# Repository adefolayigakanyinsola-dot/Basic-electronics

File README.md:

# Basic-electronics
Projects covering introduction to electronic components and systems
# Touch Enabled Circuit Design
A non microcontroller electronics project that lights up the LED when two insulated wires touch each other at the same time.
# Project Description
It is a simple project built on a breadboard. When two bare wires which serves as connectors are touched at the same time, a small amount of elevtricity passes through the skin due to low conductivity and high resistance. This in turn causes the transisitor to come on. The transistor then produces a large current from the base and battery combined which triggers the flow of current from the collector to the emitter.Then the current is passed into the LED to turn it on.

# INSTALLATION  PROCESS
# Software - KICAD
After creating a new file and nameing the circuit design,draw the schematics.
To do this,click on the component symbol icon on the top right icon bar to the side and select the components.
Use the mouse to drag and connect the wires accordingly.
Assign footprints by using the upper ico to the right on the menu bar or left click the mouse on each component,then navigate to footprints to check for suitable type of footprint component.
# PCB LAYOUT
Open the PCB bar by clicking on the default icon which is top right to the extreme,it takes you to thr layout that has all the components layout in PCB.
Using edge cuts in the apperance icon to the right,draw the small board outline enough to cover the circuit.
Arrange the components and usd the route signals to connect them 
Using the view icon in the top left icon on the menu bar,check the 3D layout.

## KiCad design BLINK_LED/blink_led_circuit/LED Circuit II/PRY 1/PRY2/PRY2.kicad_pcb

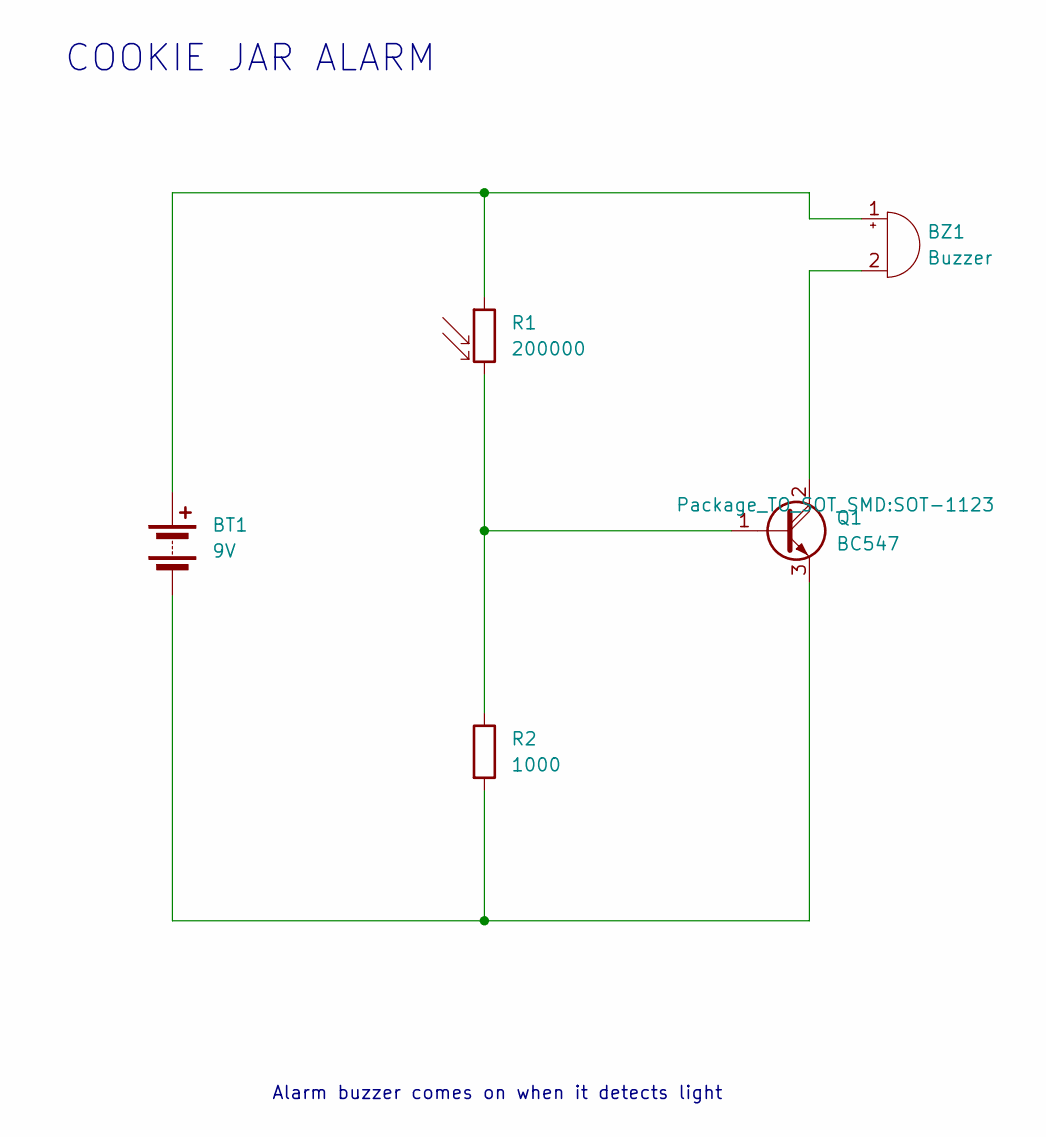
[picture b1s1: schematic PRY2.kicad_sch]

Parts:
BT1: 9V; BatteryHolder_MYOUNG_BS-07-A1BJ001_CR2032
BZ1: Buzzer; Buzzer_15x7.5RM7.6
Q1: BC547; SOT-1123
R1: 200000; R_LDR_10x8.5mm_P7.6mm_Vertical
R2: 1000; R_Axial_DIN0204_L3.6mm_D1.6mm_P5.08mm_Horizontal

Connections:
unnamed: BT1.1 (+), BZ1.1 (+), R1.1
unnamed: BT1.2 (-), Q1.3 (E), R2.2
unnamed: BZ1.2 (-), Q1.2 (C)
unnamed: Q1.1 (B), R1.2, R2.1

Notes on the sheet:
Alarm buzzer comes on when it detects light
COOKIE JAR ALARM

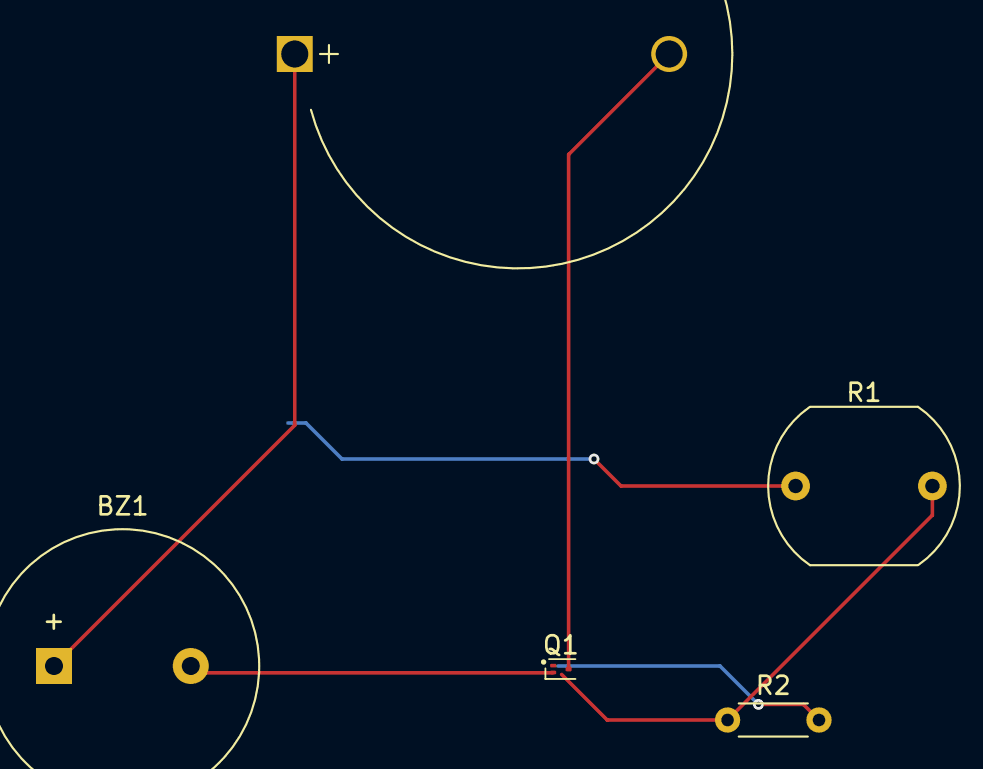
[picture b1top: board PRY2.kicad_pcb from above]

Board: 2 copper layers, 5 parts (0 on the bottom side), 4 nets.

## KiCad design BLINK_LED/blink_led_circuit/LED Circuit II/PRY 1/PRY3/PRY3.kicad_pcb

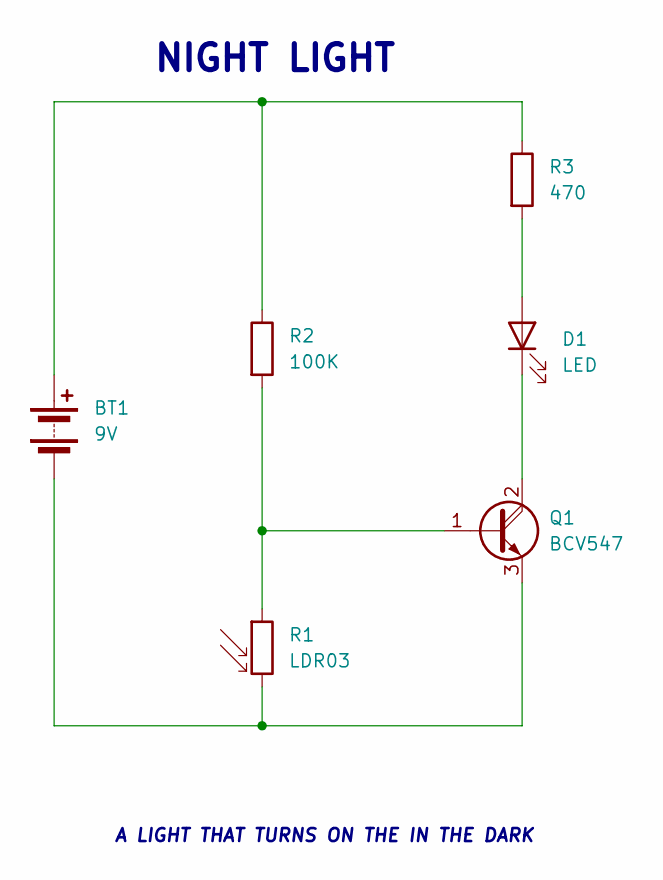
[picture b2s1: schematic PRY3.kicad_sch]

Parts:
BT1: 9V; BatteryHolder_MYOUNG_BS-07-A1BJ001_CR2032
D1: LED; LED_D2.0mm_W4.0mm_H2.8mm_FlatTop
Q1: BCV547; SOT-89-3
R1: LDR03; R_LDR_10x8.5mm_P7.6mm_Vertical
R2: 100K; R_Axial_DIN0204_L3.6mm_D1.6mm_P1.90mm_Vertical
R3: 470; R_Axial_DIN0204_L3.6mm_D1.6mm_P1.90mm_Vertical

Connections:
unnamed: BT1.1 (+), R2.1, R3.1
unnamed: BT1.2 (-), Q1.3 (E), R1.2
unnamed: D1.2 (A), R3.2
unnamed: D1.1 (K), Q1.2 (C)
unnamed: Q1.1 (B), R1.1, R2.2

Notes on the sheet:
NIGHT LIGHT
A LIGHT THAT TURNS ON THE IN THE DARK

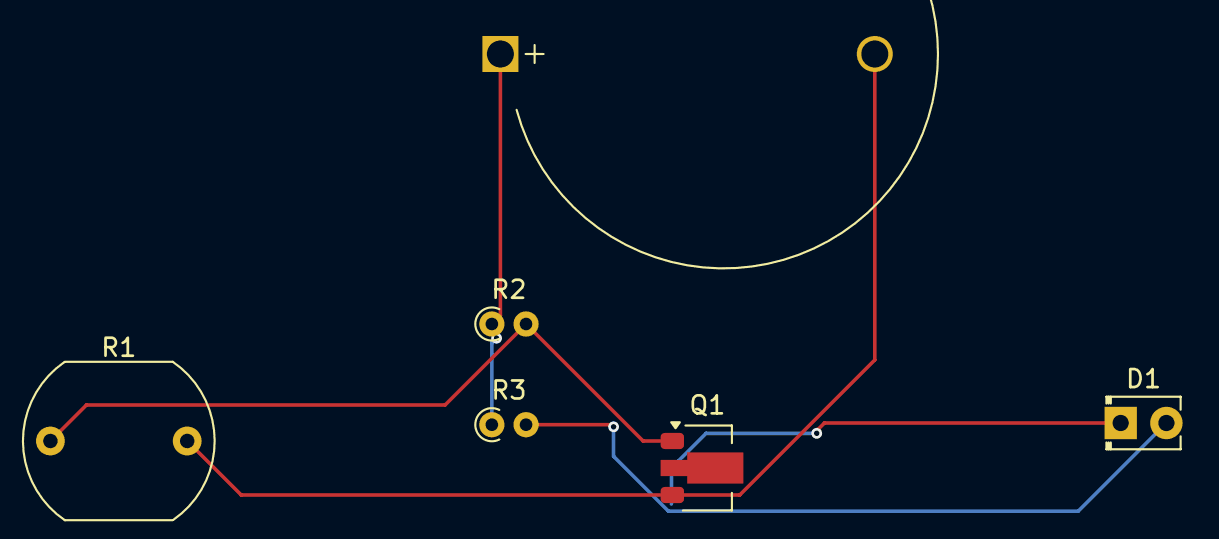
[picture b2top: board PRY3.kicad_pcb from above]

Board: 2 copper layers, 6 parts (0 on the bottom side), 5 nets.

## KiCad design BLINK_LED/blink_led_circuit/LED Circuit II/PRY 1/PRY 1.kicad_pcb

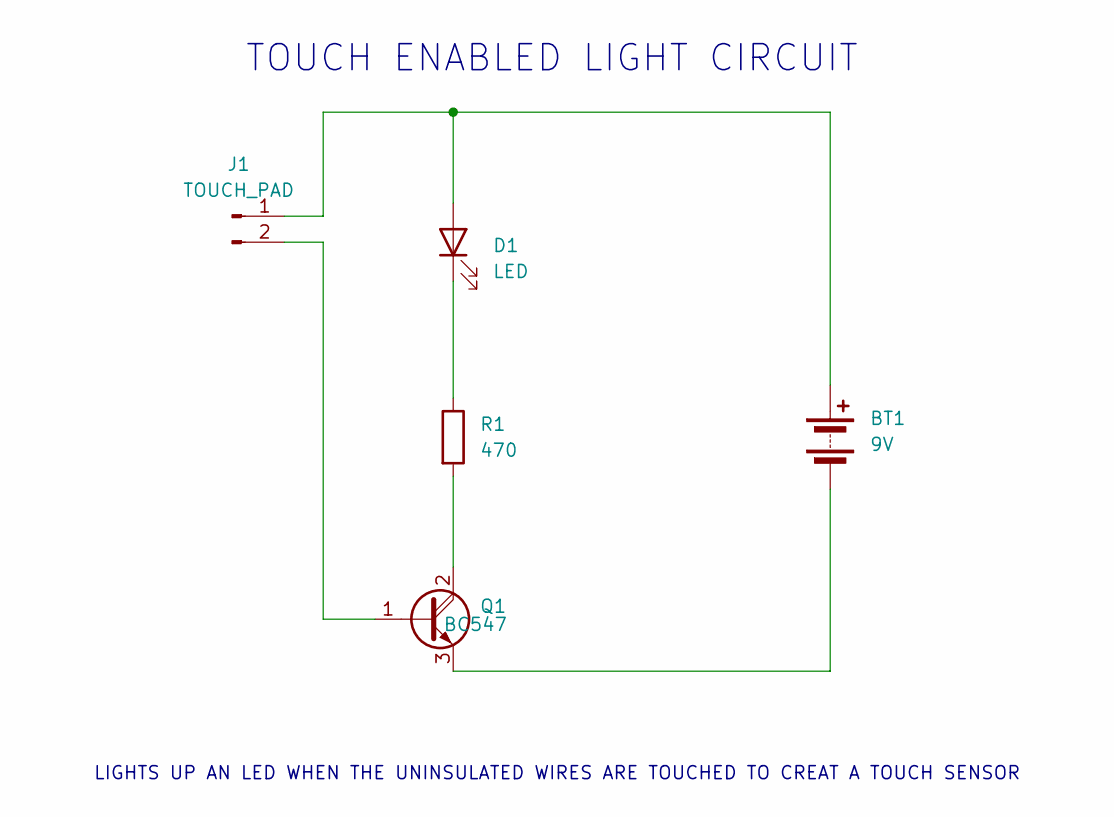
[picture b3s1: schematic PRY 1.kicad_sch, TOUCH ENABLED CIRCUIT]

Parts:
BT1: 9V; BatteryHolder_Keystone_1057_1x2032
D1: LED; LED_D2.0mm_W4.8mm_H2.5mm_FlatTop
J1: TOUCH_PAD; JWT_A3963_1x02_P3.96mm_Vertical
Q1: BC547; SOT-89-3
R1: 470; R_Axial_DIN0204_L3.6mm_D1.6mm_P2.54mm_Vertical

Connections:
unnamed: BT1.1 (+), D1.2 (A), J1.1
unnamed: BT1.2 (-), Q1.3 (E)
unnamed: D1.1 (K), R1.1
unnamed: J1.2, Q1.1 (B)
unnamed: Q1.2 (C), R1.2

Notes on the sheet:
TOUCH ENABLED LIGHT CIRCUIT
LIGHTS UP AN LED WHEN THE UNINSULATED WIRES ARE TOUCHED TO CREAT A TOUCH SENSOR

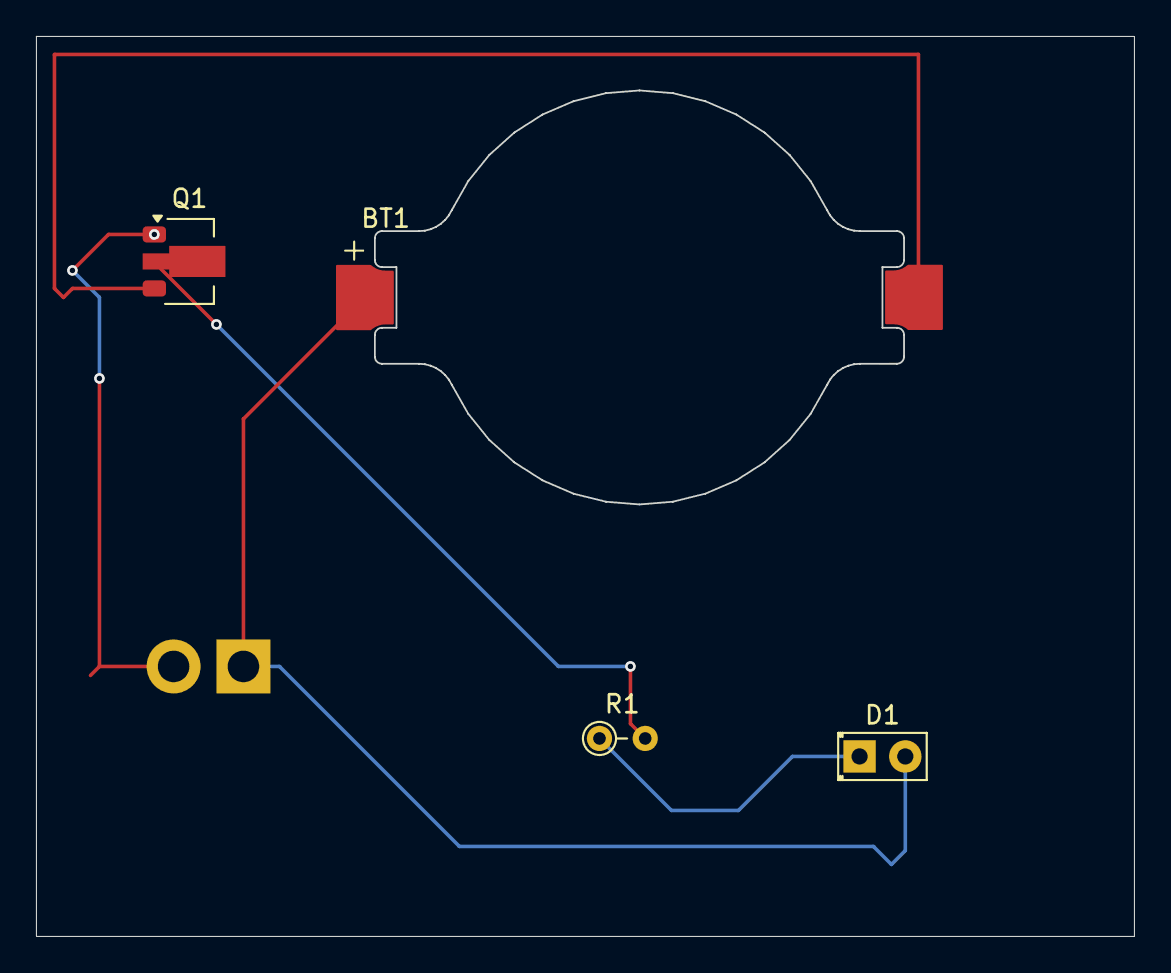
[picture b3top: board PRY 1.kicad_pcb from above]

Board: 2 copper layers, 60.9 x 50.0 mm, 5 parts (1 on the bottom side), 5 nets.

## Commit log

2026-03-27 TWO CIRCUITS: analog and digital
2026-03-27 Added arduino code and it works!
2026-03-27 deleted kicad git
2026-05-05 Added touch enabled circuit
2026-05-09 Possible errors here
2026-05-09 Added ignored changes
2026-05-09 Dealt with Kicad history issue
